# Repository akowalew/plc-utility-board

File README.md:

# plc-utility-board
Utility board designed to work with PLC controller, which contains logic level shifters and motors controllers.

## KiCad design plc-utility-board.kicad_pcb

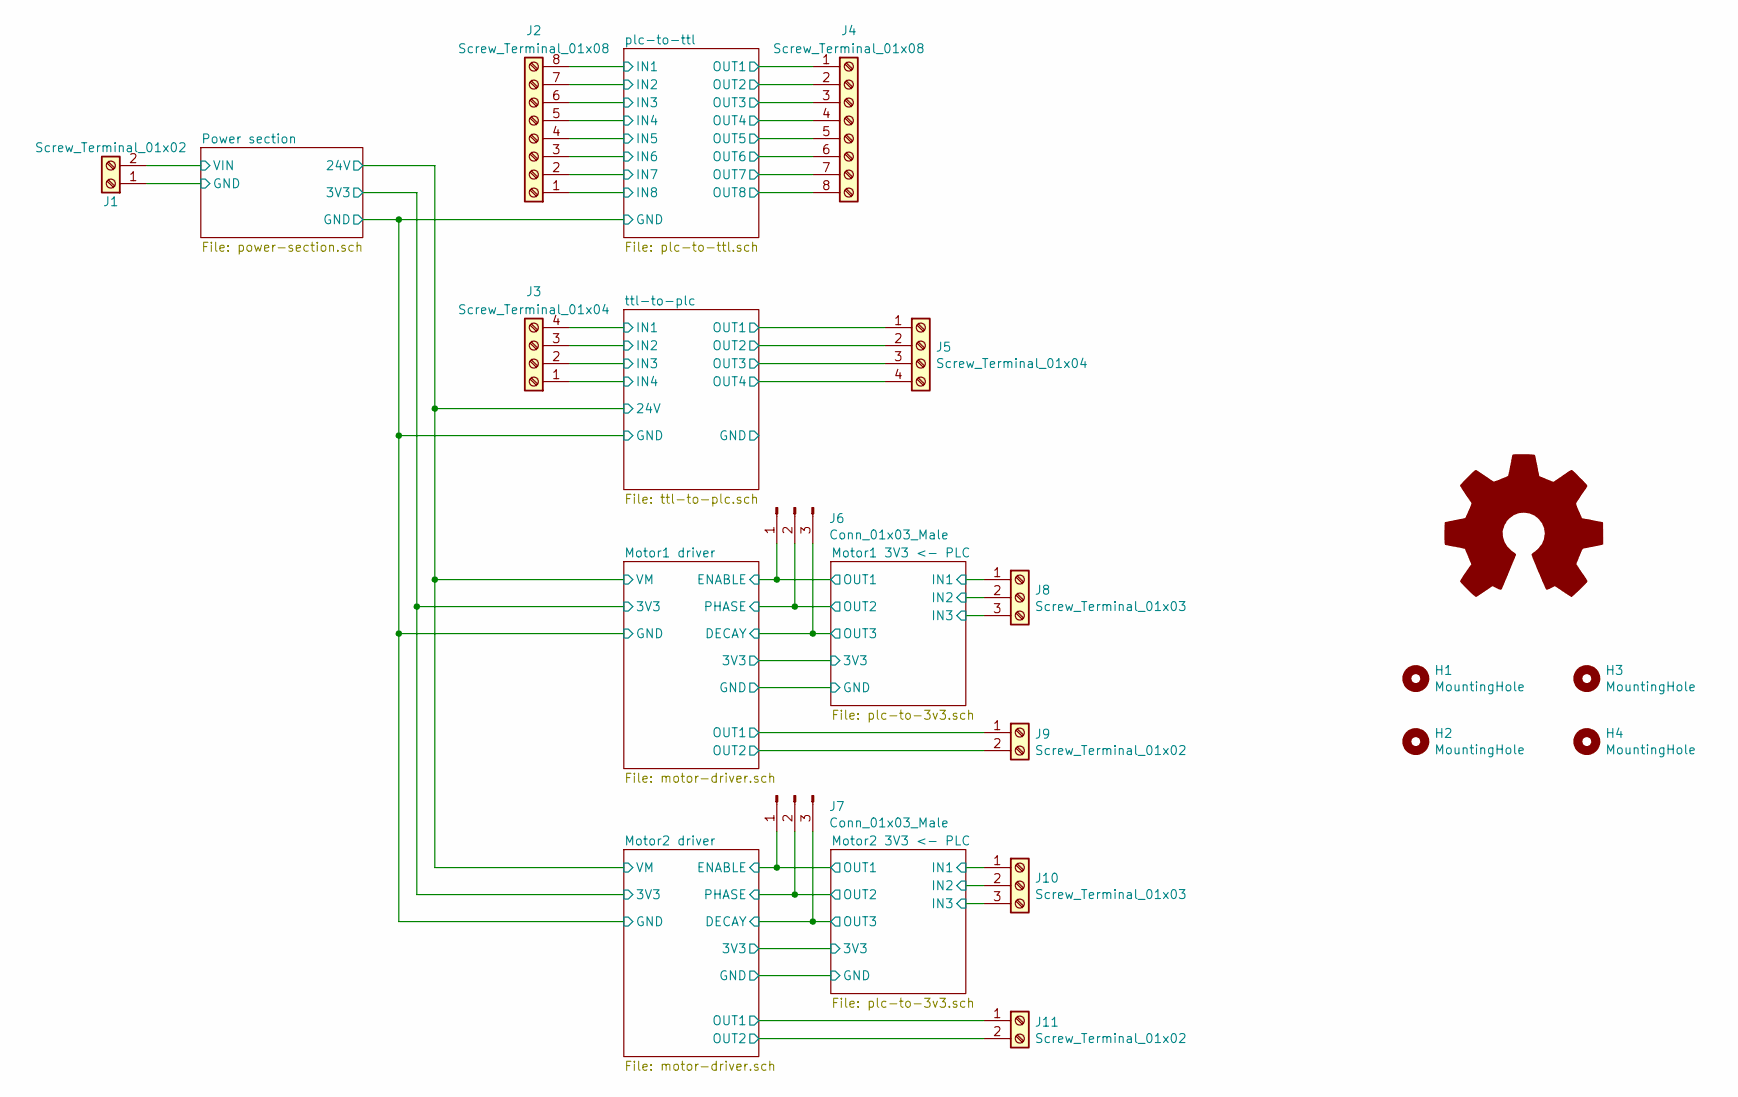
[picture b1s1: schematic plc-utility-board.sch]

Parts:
H1, H2, H3, H4: MountingHole; MountingHole_3.2mm_M3_Pad_Via
J1, J9, J11: Screw_Terminal_01x02; TerminalBlock_Phoenix_MKDS-1,5-2-5.08_1x02_P5.08mm_Horizont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
J2, J4: Screw_Terminal_01x08; TerminalBlock_Phoenix_MKDS-1,5-8-5.08_1x08_P5.08mm_Horizont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
J3, J5: Screw_Terminal_01x04; TerminalBlock_Phoenix_MKDS-1,5-4-5.08_1x04_P5.08mm_Horizont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
J6, J7: Conn_01x03_Male; PinHeader_1x03_P2.54mm_Vertical
J8, J10: Screw_Terminal_01x03; TerminalBlock_Phoenix_MKDS-1,5-3-5.08_1x03_P5.08mm_Horizont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

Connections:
/Motor1 3V3 <- PLC/IN1: J8.1; also elsewhere on the board
/Motor1 3V3 <- PLC/IN2: J8.2; also elsewhere on the board
/Motor1 3V3 <- PLC/IN3: J8.3; also elsewhere on the board
/Motor1 3V3 <- PLC/OUT2: J6.2; also elsewhere on the board
/Motor1 driver/DECAY: J6.3; also elsewhere on the board
/Motor1 driver/ENABLE: J6.1; also elsewhere on the board
/Motor1 driver/OUT1: J9.1; also elsewhere on the board
/Motor1 driver/OUT2: J9.2; also elsewhere on the board
/Motor2 3V3 <- PLC/IN1: J10.1; also elsewhere on the board
/Motor2 3V3 <- PLC/IN2: J10.2; also elsewhere on the board
/Motor2 3V3 <- PLC/IN3: J10.3; also elsewhere on the board
/Motor2 3V3 <- PLC/OUT2: J7.2; also elsewhere on the board
/Motor2 driver/DECAY: J7.3; also elsewhere on the board
/Motor2 driver/ENABLE: J7.1; also elsewhere on the board
/Motor2 driver/OUT1: J11.1; also elsewhere on the board
/Motor2 driver/OUT2: J11.2; also elsewhere on the board
/Power section/VIN: J1.2; also elsewhere on the board
/plc-to-ttl/IN1: J2.8; also elsewhere on the board
/plc-to-ttl/IN2: J2.7; also elsewhere on the board
/plc-to-ttl/IN3: J2.6; also elsewhere on the board
/plc-to-ttl/IN4: J2.5; also elsewhere on the board
/plc-to-ttl/IN5: J2.4; also elsewhere on the board
/plc-to-ttl/IN6: J2.3; also elsewhere on the board
/plc-to-ttl/IN7: J2.2; also elsewhere on the board
/plc-to-ttl/IN8: J2.1; also elsewhere on the board
/plc-to-ttl/OUT1: J4.1; also elsewhere on the board
/plc-to-ttl/OUT2: J4.2; also elsewhere on the board
/plc-to-ttl/OUT3: J4.3; also elsewhere on the board
/plc-to-ttl/OUT4: J4.4; also elsewhere on the board
/plc-to-ttl/OUT5: J4.5; also elsewhere on the board
/plc-to-ttl/OUT6: J4.6; also elsewhere on the board
/plc-to-ttl/OUT7: J4.7; also elsewhere on the board
/plc-to-ttl/OUT8: J4.8; also elsewhere on the board
/ttl-to-plc/IN1: J3.4; also elsewhere on the board
/ttl-to-plc/IN2: J3.3; also elsewhere on the board
/ttl-to-plc/IN3: J3.2; also elsewhere on the board
/ttl-to-plc/IN4: J3.1; also elsewhere on the board
/ttl-to-plc/OUT1: J5.1; also elsewhere on the board
/ttl-to-plc/OUT2: J5.2; also elsewhere on the board
/ttl-to-plc/OUT3: J5.3; also elsewhere on the board
/ttl-to-plc/OUT4: J5.4; also elsewhere on the board
GND: J1.1; also elsewhere on the board

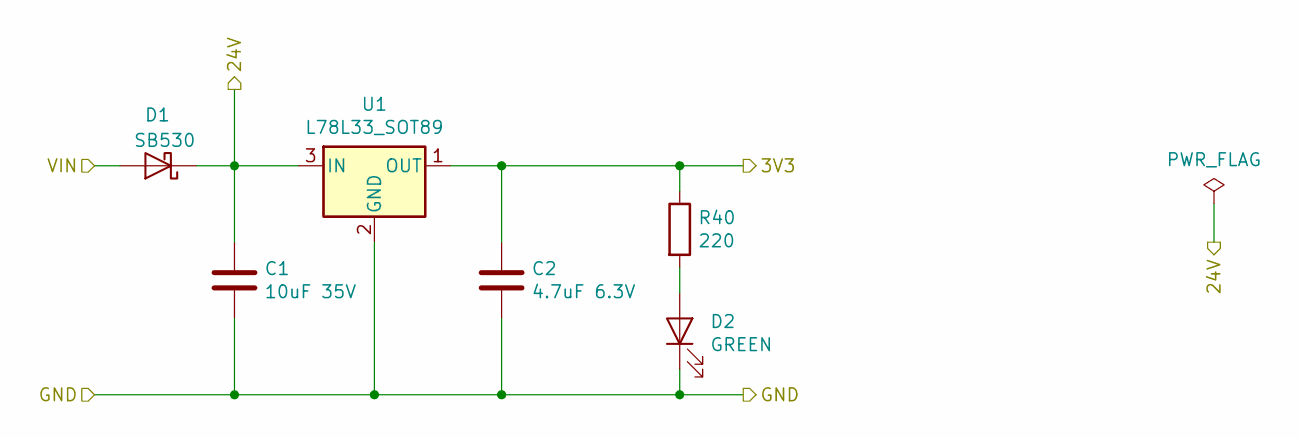
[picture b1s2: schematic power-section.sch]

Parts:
C1: 10uF 35V; C_1210_3225Metric_Pad1.42x2.65mm_HandSolder
C2: 4.7uF 6.3V; C_0805_2012Metric_Pad1.15x1.40mm_HandSolder
D1: SB530; D_DO-201AD_P5.08mm_Vertical_KathodeUp
D2: GREEN; LED_0603_1608Metric_Castellated
R40: 220; R_0603_1608Metric
U1: L78L33_SOT89; SOT-89-3_Handsoldering

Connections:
/Motor1 3V3 <- PLC/3V3: C2.1, R40.1, U1.1 (OUT); also elsewhere on the board
/Power section/24V: C1.1, D1.1 (K), U1.3 (IN); also elsewhere on the board
/Power section/VIN: D1.2 (A); also elsewhere on the board
GND: C1.2, C2.2, D2.1 (K), U1.2 (GND); also elsewhere on the board
unnamed: D2.2 (A), R40.2

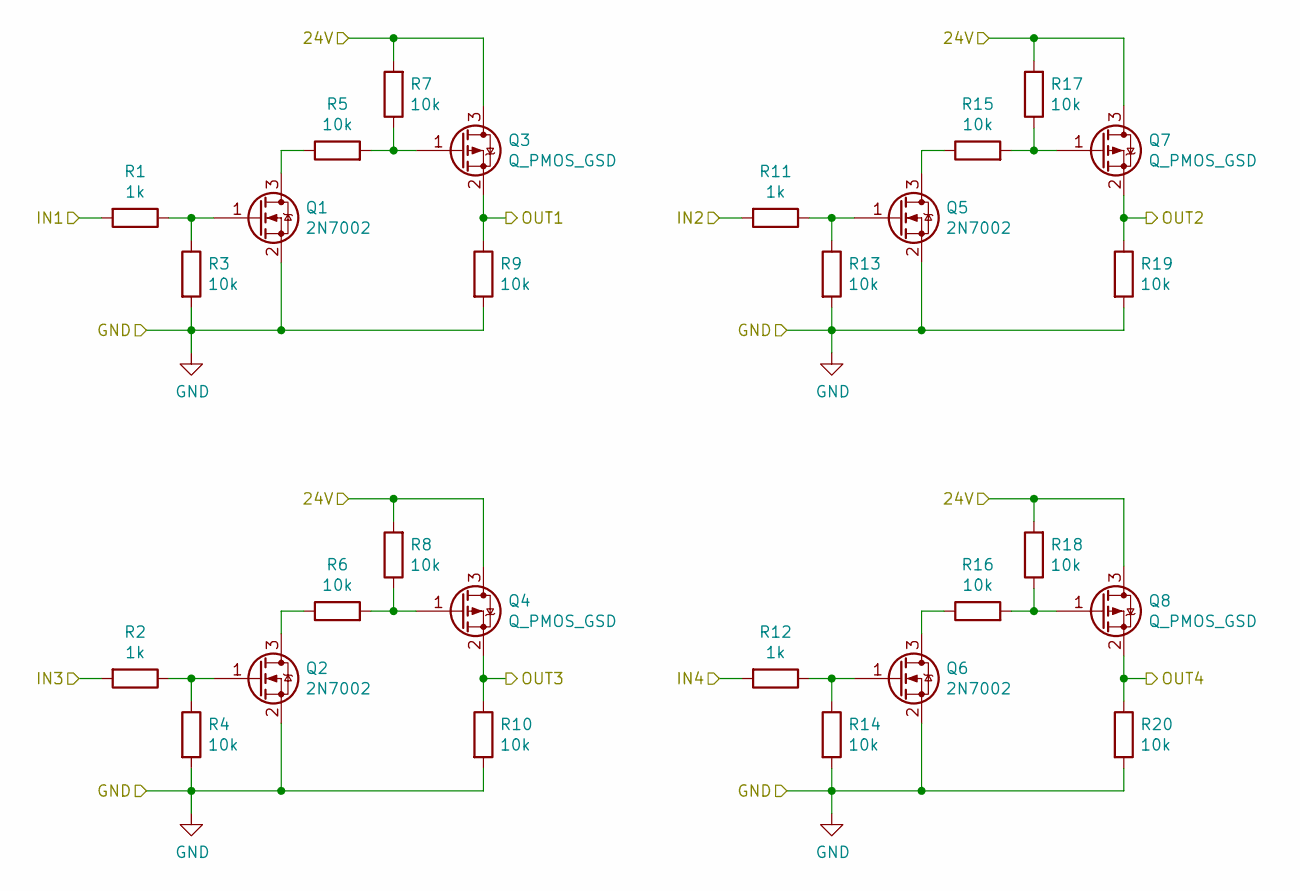
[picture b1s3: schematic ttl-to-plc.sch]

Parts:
Q1, Q2, Q5, Q6: 2N7002; SOT-23
Q3, Q4, Q7, Q8: Q_PMOS_GSD; SOT-23
R1, R2, R11, R12: 1k; R_0603_1608Metric
R3, R4, R5, R6, R7, R8, R9, R10, R13, R14, R15, R16, R17, R18, R19, R20: 10k; R_0603_1608Metric

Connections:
/Power section/24V: Q3.3 (D), Q4.3 (D), Q7.3 (D), Q8.3 (D), R7.2, R8.2, R17.2, R18.2; also elsewhere on the board
/ttl-to-plc/IN1: R1.2; also elsewhere on the board
/ttl-to-plc/IN2: R11.2; also elsewhere on the board
/ttl-to-plc/IN3: R2.2; also elsewhere on the board
/ttl-to-plc/IN4: R12.2; also elsewhere on the board
/ttl-to-plc/OUT1: Q3.2 (S), R9.1; also elsewhere on the board
/ttl-to-plc/OUT2: Q7.2 (S), R19.1; also elsewhere on the board
/ttl-to-plc/OUT3: Q4.2 (S), R10.1; also elsewhere on the board
/ttl-to-plc/OUT4: Q8.2 (S), R20.1; also elsewhere on the board
GND: Q1.2 (S), Q2.2 (S), Q5.2 (S), Q6.2 (S), R3.2, R4.2, R9.2, R10.2, R13.2, R14.2, R19.2, R20.2; also elsewhere on the board
unnamed: Q1.1 (G), R1.1, R3.1
unnamed: Q1.3 (D), R5.1
unnamed: Q2.1 (G), R2.1, R4.1
unnamed: Q2.3 (D), R6.1
unnamed: Q3.1 (G), R5.2, R7.1
unnamed: Q4.1 (G), R6.2, R8.1
unnamed: Q5.1 (G), R11.1, R13.1
unnamed: Q5.3 (D), R15.1
unnamed: Q6.1 (G), R12.1, R14.1
unnamed: Q6.3 (D), R16.1
unnamed: Q7.1 (G), R15.2, R17.1
unnamed: Q8.1 (G), R16.2, R18.1

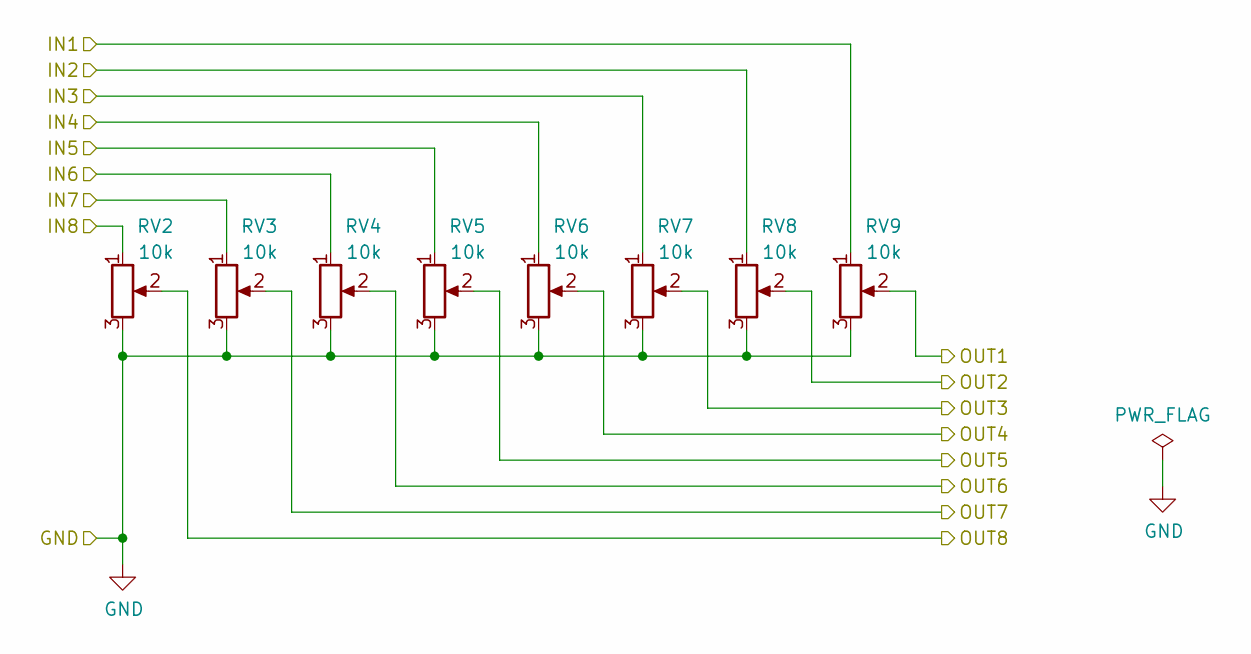
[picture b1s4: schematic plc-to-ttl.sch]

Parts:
RV2, RV3, RV4, RV5, RV6, RV7, RV8, RV9: 10k; Potentiometer_Bourns_3296Y_Vertical

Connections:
/plc-to-ttl/IN1: RV9.1; also elsewhere on the board
/plc-to-ttl/IN2: RV8.1; also elsewhere on the board
/plc-to-ttl/IN3: RV7.1; also elsewhere on the board
/plc-to-ttl/IN4: RV6.1; also elsewhere on the board
/plc-to-ttl/IN5: RV5.1; also elsewhere on the board
/plc-to-ttl/IN6: RV4.1; also elsewhere on the board
/plc-to-ttl/IN7: RV3.1; also elsewhere on the board
/plc-to-ttl/IN8: RV2.1; also elsewhere on the board
/plc-to-ttl/OUT1: RV9.2; also elsewhere on the board
/plc-to-ttl/OUT2: RV8.2; also elsewhere on the board
/plc-to-ttl/OUT3: RV7.2; also elsewhere on the board
/plc-to-ttl/OUT4: RV6.2; also elsewhere on the board
/plc-to-ttl/OUT5: RV5.2; also elsewhere on the board
/plc-to-ttl/OUT6: RV4.2; also elsewhere on the board
/plc-to-ttl/OUT7: RV3.2; also elsewhere on the board
/plc-to-ttl/OUT8: RV2.2; also elsewhere on the board
GND: RV2.3, RV3.3, RV4.3, RV5.3, RV6.3, RV7.3, RV8.3, RV9.3; also elsewhere on the board

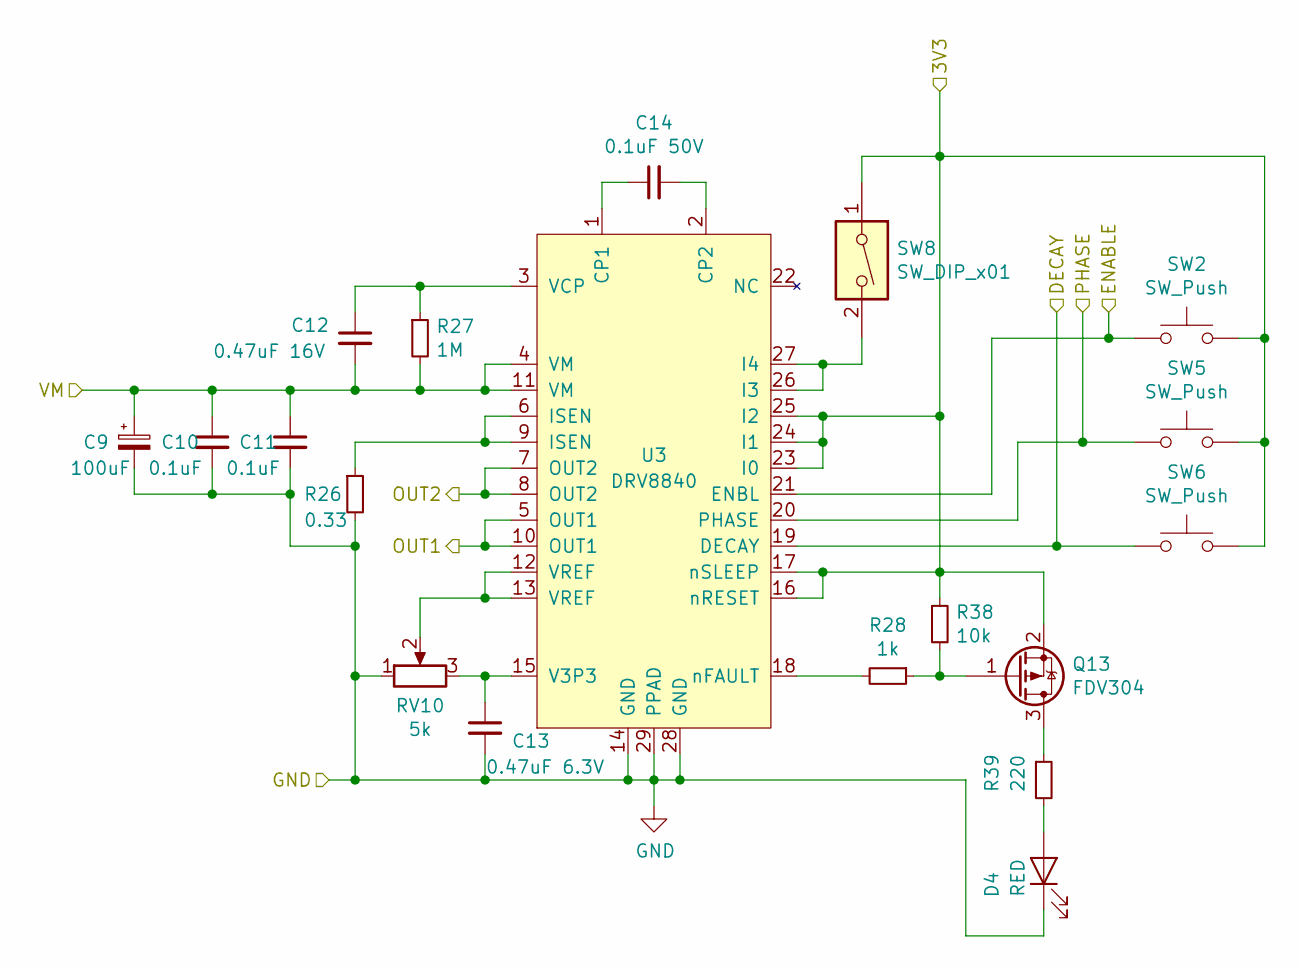
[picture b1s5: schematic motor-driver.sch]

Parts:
C3: 100uF; CP_Radial_D6.3mm_P2.50mm
C4, C5: 0.1uF; C_0603_1608Metric
C6: 0.47uF 16V; C_0603_1608Metric
C7: 0.47uF 6.3V; C_0603_1608Metric
C8: 0.1uF 50V; C_0603_1608Metric
D3: RED; LED_0603_1608Metric_Castellated
Q13: FDV304; SOT-23
R21: 0.33; R_2512_6332Metric
R22: 1M; R_0603_1608Metric
R23: 1k; R_0603_1608Metric
R24: 10k; R_0603_1608Metric
R25: 220; R_0603_1608Metric
RV1: 5k; Potentiometer_Bourns_3266W_Vertical
SW1, SW3, SW4: SW_Push; SW_SPST_KMR2
SW7: SW_DIP_x01; CHS01TB
U2: DRV8840; SOP65P640X110-29N

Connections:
/Motor1 3V3 <- PLC/3V3: Q13.2 (S), R24.1, SW1.2, SW3.2, SW4.2, SW7.1, U2.16 (nRESET), U2.17 (nSLEEP), U2.23 (I0), U2.24 (I1), U2.25 (I2); also elsewhere on the board
/Motor1 3V3 <- PLC/OUT2: SW3.1, U2.20 (PHASE); also elsewhere on the board
/Motor1 driver/DECAY: SW4.1, U2.19 (DECAY); also elsewhere on the board
/Motor1 driver/ENABLE: SW1.1, U2.21 (ENBL); also elsewhere on the board
/Motor1 driver/OUT1: U2.5 (OUT1), U2.10 (OUT1); also elsewhere on the board
/Motor1 driver/OUT2: U2.7 (OUT2), U2.8 (OUT2); also elsewhere on the board
/Power section/24V: C3.1, C4.1, C5.1, C6.2, R22.2, U2.4 (VM), U2.11 (VM); also elsewhere on the board
GND: C3.2, C4.2, C5.2, C7.2, D3.1 (K), R21.2, RV1.1, U2.14 (GND), U2.28 (GND), U2.29 (PPAD); also elsewhere on the board
unnamed: C6.1, R22.1, U2.3 (VCP)
unnamed: C7.1, RV1.3, U2.15 (V3P3)
unnamed: C8.1, U2.1 (CP1)
unnamed: C8.2, U2.2 (CP2)
unnamed: D3.2 (A), R25.2
unnamed: R21.1, U2.6 (ISEN), U2.9 (ISEN)
unnamed: R23.2, U2.18 (nFAULT)
unnamed: RV1.2, U2.12 (VREF), U2.13 (VREF)
unnamed: SW7.2, U2.26 (I3), U2.27 (I4)

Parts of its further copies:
C9: 100uF; CP_Radial_D6.3mm_P2.50mm
C10, C11: 0.1uF; C_0603_1608Metric
C12: 0.47uF 16V; C_0603_1608Metric
C13: 0.47uF 6.3V; C_0603_1608Metric
C14: 0.1uF 50V; C_0603_1608Metric
D4: RED; LED_0603_1608Metric_Castellated
Q9: FDV304; SOT-23
R26: 0.33; R_2512_6332Metric
R27: 1M; R_0603_1608Metric
R28: 1k; R_0603_1608Metric
R38: 10k; R_0603_1608Metric
R39: 220; R_0603_1608Metric
RV10: 5k; Potentiometer_Bourns_3266W_Vertical
SW2, SW5, SW6: SW_Push; SW_SPST_KMR2
SW8: SW_DIP_x01; CHS01TB
U3: DRV8840; SOP65P640X110-29N

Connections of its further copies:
/Motor1 3V3 <- PLC/3V3: Q9.2 (S), R38.1, SW2.2, SW5.2, SW6.2, SW8.1, U3.16 (nRESET), U3.17 (nSLEEP), U3.23 (I0), U3.24 (I1), U3.25 (I2); also elsewhere on the board
/Motor2 3V3 <- PLC/OUT2: SW5.1, U3.20 (PHASE); also elsewhere on the board
/Motor2 driver/DECAY: SW6.1, U3.19 (DECAY); also elsewhere on the board
/Motor2 driver/ENABLE: SW2.1, U3.21 (ENBL); also elsewhere on the board
/Motor2 driver/OUT1: U3.5 (OUT1), U3.10 (OUT1); also elsewhere on the board
/Motor2 driver/OUT2: U3.7 (OUT2), U3.8 (OUT2); also elsewhere on the board
/Power section/24V: C9.1, C10.1, C11.1, C12.2, R27.2, U3.4 (VM), U3.11 (VM); also elsewhere on the board
GND: C9.2, C10.2, C11.2, C13.2, D4.1 (K), R26.2, RV10.1, U3.14 (GND), U3.28 (GND), U3.29 (PPAD); also elsewhere on the board
unnamed: C12.1, R27.1, U3.3 (VCP)
unnamed: C13.1, RV10.3, U3.15 (V3P3)
unnamed: C14.1, U3.1 (CP1)
unnamed: C14.2, U3.2 (CP2)
unnamed: D4.2 (A), R39.2
unnamed: R26.1, U3.6 (ISEN), U3.9 (ISEN)
unnamed: R28.2, U3.18 (nFAULT)
unnamed: RV10.2, U3.12 (VREF), U3.13 (VREF)
unnamed: SW8.2, U3.26 (I3), U3.27 (I4)

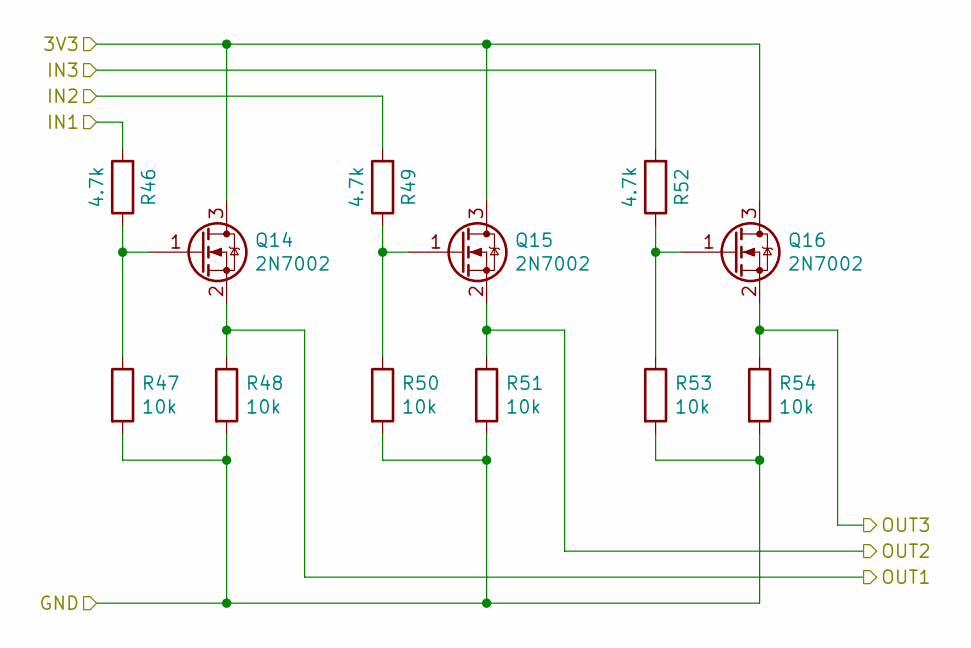
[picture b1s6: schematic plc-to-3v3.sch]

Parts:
Q10, Q11, Q12: 2N7002; SOT-23
R29, R32, R35: 4.7k; R_0603_1608Metric
R30, R31, R33, R34, R36, R37: 10k; R_0603_1608Metric

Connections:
/Motor1 3V3 <- PLC/3V3: Q10.3 (D), Q11.3 (D), Q12.3 (D); also elsewhere on the board
/Motor1 3V3 <- PLC/IN1: R29.2; also elsewhere on the board
/Motor1 3V3 <- PLC/IN2: R32.2; also elsewhere on the board
/Motor1 3V3 <- PLC/IN3: R35.2; also elsewhere on the board
/Motor1 3V3 <- PLC/OUT2: Q11.2 (S), R34.1; also elsewhere on the board
/Motor1 driver/DECAY: Q12.2 (S), R37.1; also elsewhere on the board
/Motor1 driver/ENABLE: Q10.2 (S), R31.1; also elsewhere on the board
GND: R30.2, R31.2, R33.2, R34.2, R36.2, R37.2; also elsewhere on the board
unnamed: Q10.1 (G), R29.1, R30.1
unnamed: Q11.1 (G), R32.1, R33.1
unnamed: Q12.1 (G), R35.1, R36.1

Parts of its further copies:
Q14, Q15, Q16: 2N7002; SOT-23
R46, R49, R52: 4.7k; R_0603_1608Metric
R47, R48, R50, R51, R53, R54: 10k; R_0603_1608Metric

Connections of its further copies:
/Motor1 3V3 <- PLC/3V3: Q14.3 (D), Q15.3 (D), Q16.3 (D); also elsewhere on the board
/Motor2 3V3 <- PLC/IN1: R46.2; also elsewhere on the board
/Motor2 3V3 <- PLC/IN2: R49.2; also elsewhere on the board
/Motor2 3V3 <- PLC/IN3: R52.2; also elsewhere on the board
/Motor2 3V3 <- PLC/OUT2: Q15.2 (S), R51.1; also elsewhere on the board
/Motor2 driver/DECAY: Q16.2 (S), R54.1; also elsewhere on the board
/Motor2 driver/ENABLE: Q14.2 (S), R48.1; also elsewhere on the board
GND: R47.2, R48.2, R50.2, R51.2, R53.2, R54.2; also elsewhere on the board
unnamed: Q14.1 (G), R46.1, R47.1
unnamed: Q15.1 (G), R49.1, R50.1
unnamed: Q16.1 (G), R52.1, R53.1

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
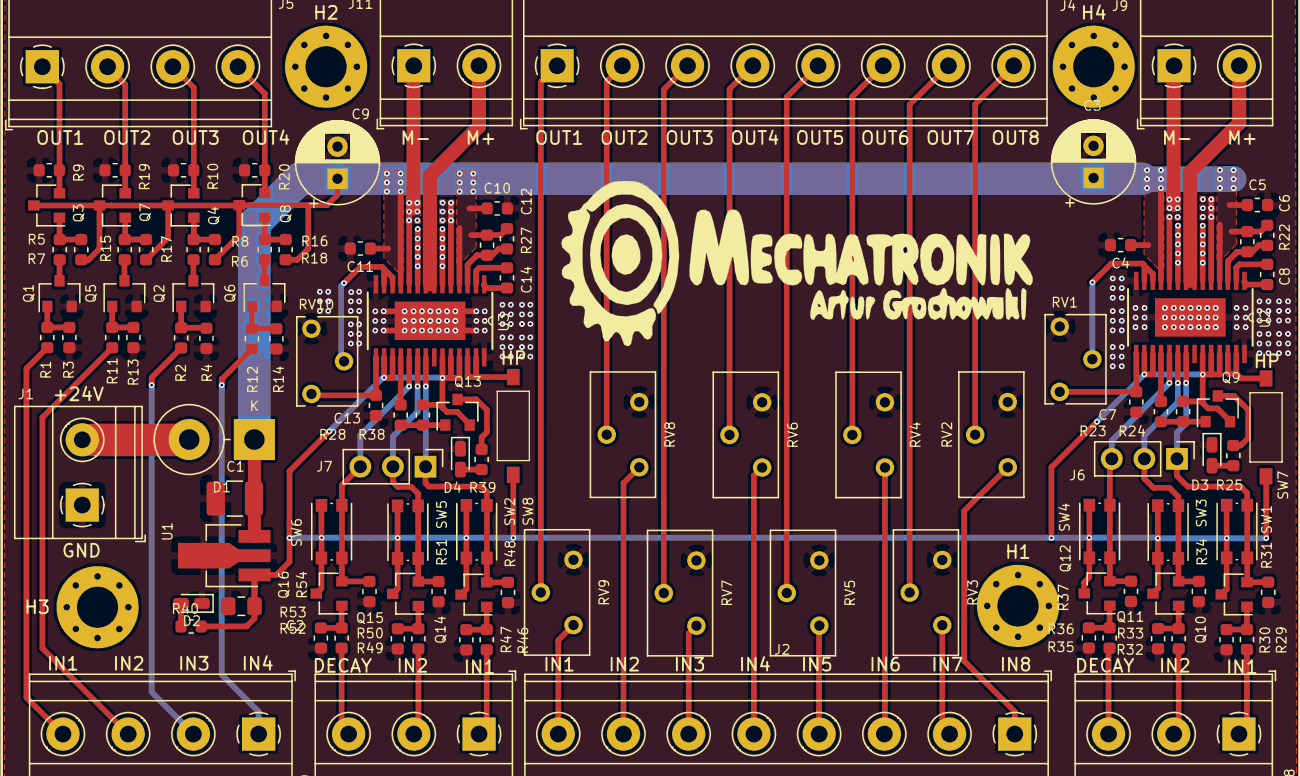
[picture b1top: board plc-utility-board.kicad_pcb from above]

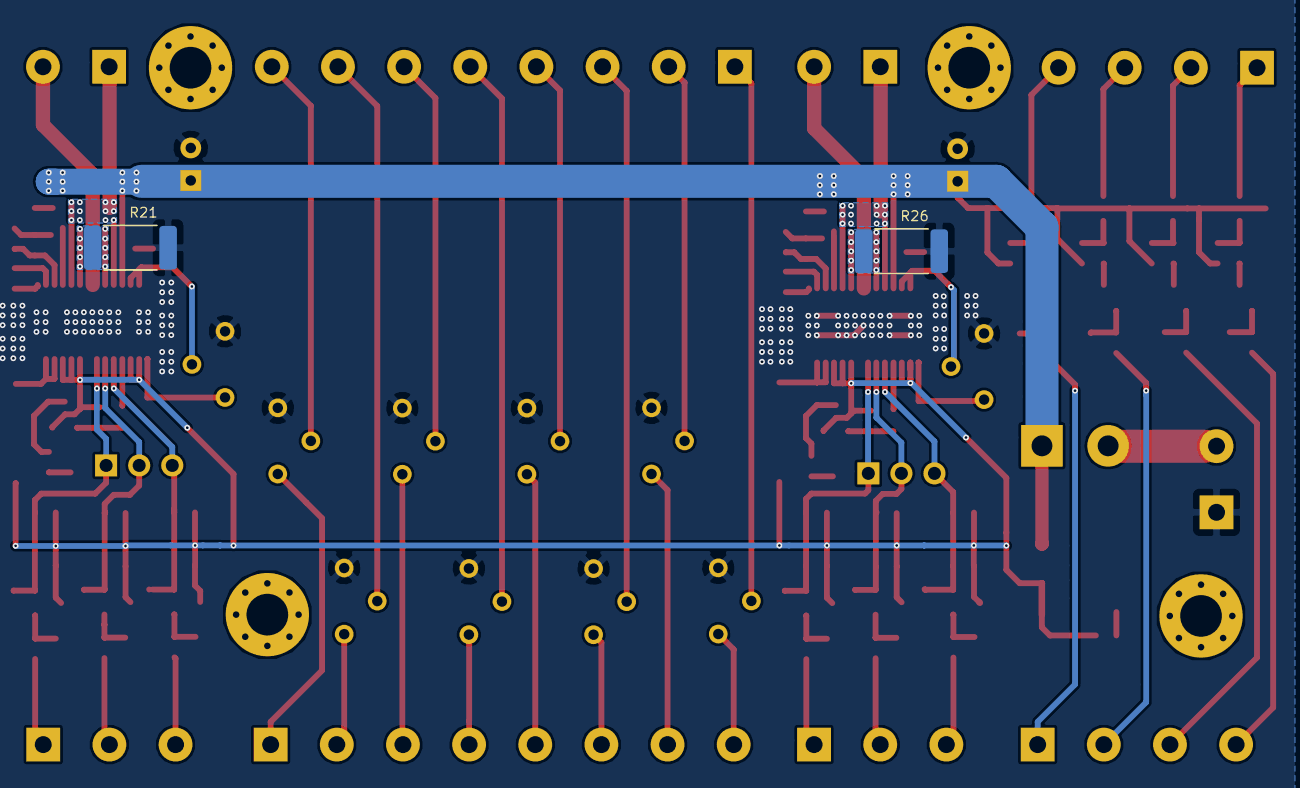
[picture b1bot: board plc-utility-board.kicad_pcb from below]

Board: 2 copper layers, 119 parts (2 on the bottom side), 85 nets.

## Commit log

2018-10-30 Near full project. Missing power supply section and connection between sheets
2018-10-31 Added Green LED for signalling VBB
2018-10-31 Added MAX15062 as 3.3V power supply
2018-10-31 ttl->plc: replaced BC546 with 2N7002 to comply with typical logic levels voltages in Arduino
2018-10-31 plc->ttl: Small correction of wires arangement
2018-11-01 Reorganized everything to use hierarchical sheets in KiCAD. Moved power supply section for motor driver into separate sheet. Moved connectors into top-level sheet
2018-11-02 Generated annotations, netlists and assigned footprints into components
2018-11-03 Added sketch of PCB. Added circuits for PLC->TTL converter. Modified shape of DG500 component to comply with Phoenix's one
2018-11-03 Added power supply section to PCB. Added missing components footprints.
2018-11-04 PCB creation, improvements of power supply section
2018-11-05 Further work at PCB
2018-11-16 Changed Motor Controller to DRV8840, removed pre-motor power section. Replaced PNP transistors in logic level shifters with P-MOSFET units
2018-11-16 Re-placed components of 3.3->24V converter. Improvement placement of Motor Controller components
2018-11-18 Aligned references of components. Duplicated motor controller section
2018-11-18 Routed all nets without GND. Added logo
2018-11-18 Added HTSSOP 28 3d model for motor controller
2018-11-18 Added elapsed 3D models for components
2018-11-19 Added switch for selecting Low/High power motor. Added thermal pads around motor controllers.
2018-11-19 Added GND zones. Changed priority of motor controllers voltage zones to 1. Added labels to terminal blocks
2018-11-20 Altered connections of button switch to decay pin from GND to 3.3V (also removed unnecessary resistor)
2018-11-21 Added mounting holes for M3 screws. Performed DRC check.
